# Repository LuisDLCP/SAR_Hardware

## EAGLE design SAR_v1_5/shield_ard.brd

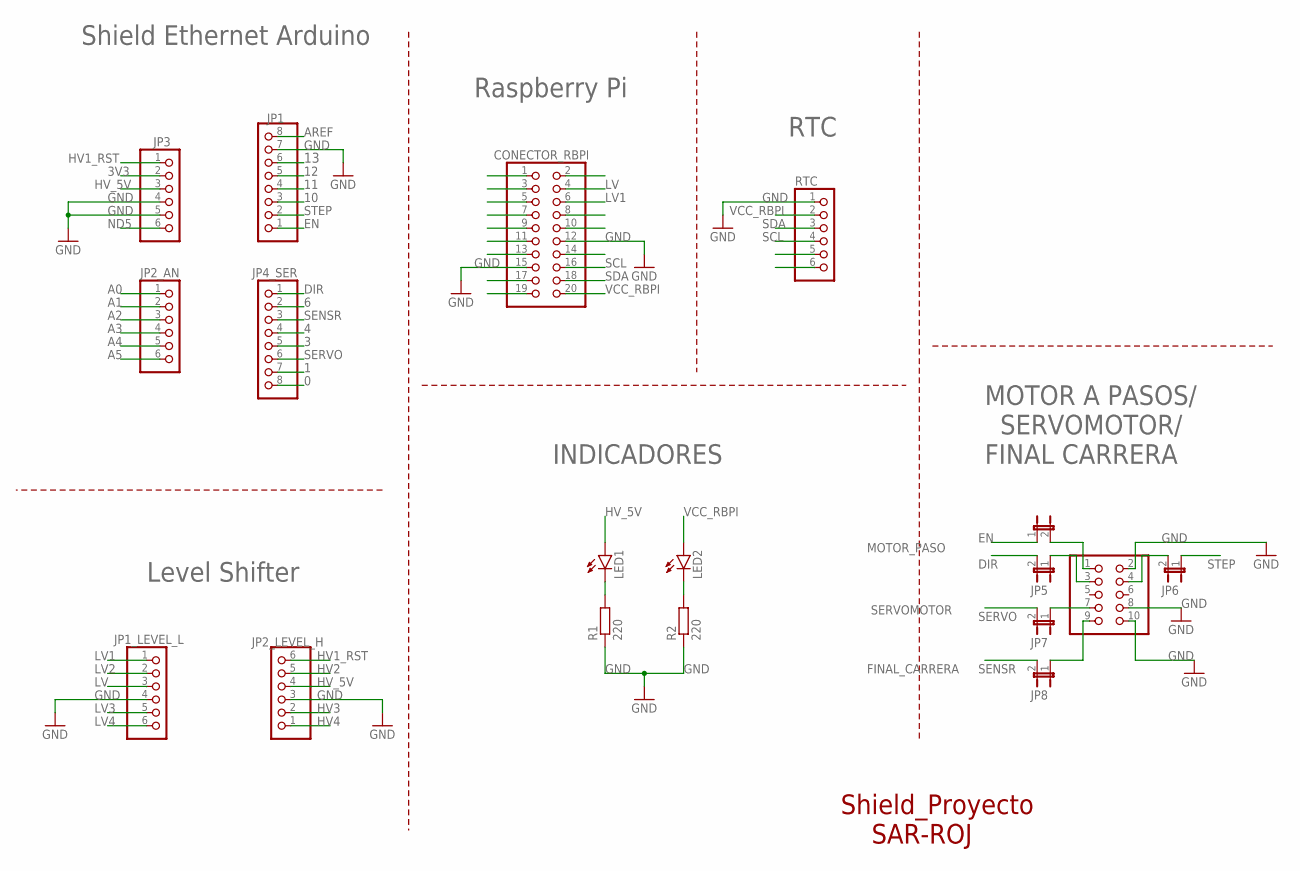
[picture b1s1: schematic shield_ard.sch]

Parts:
CONECTOR_RBPI: PINHD-2X10; 2X10
JP1, JP4_SER: PINHD-1X8; 1X08
JP1_LEVEL_L, JP2_AN, JP2_LEVEL_H, JP3: PINHD-1X6; 1X06
JP2, JP5, JP6, JP7, JP8: JUMPER-2PTH; 1X02
LED1, LED2: LEDCHIP-LED0805; CHIP-LED0805
MOTOR_PASO: PINHD-2X5; 2X05
R1, R2: 220; R0805
RTC: PINHD-1X6/90; 1X06/90

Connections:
0: JP4_SER.8
1: JP4_SER.7
3: JP4_SER.5
3V3: JP3.2
4: JP4_SER.4
6: JP4_SER.2
10: JP1.3
11: JP1.4
12: JP1.5
13: JP1.6
A0: JP2_AN.1
A1: JP2_AN.2
A2: JP2_AN.3
A3: JP2_AN.4
A4: JP2_AN.5
A5: JP2_AN.6
AREF: JP1.8
DIR: JP4_SER.1, JP5.1, JP5.2, MOTOR_PASO.3
EN: JP1.1, JP2.1, JP2.2, MOTOR_PASO.1
GND: CONECTOR_RBPI.12, CONECTOR_RBPI.15, JP1.7, JP1_LEVEL_L.4, JP2_LEVEL_H.3, JP3.4, JP3.5, MOTOR_PASO.2, MOTOR_PASO.8, MOTOR_PASO.10, R1.1, R2.1, RTC.1
HV1_RST: JP2_LEVEL_H.6, JP3.1
HV2: JP2_LEVEL_H.5
HV3: JP2_LEVEL_H.2
HV4: JP2_LEVEL_H.1
HV_5V: JP2_LEVEL_H.4, JP3.3, LED1.A
LV: CONECTOR_RBPI.4, JP1_LEVEL_L.3
LV1: CONECTOR_RBPI.6, JP1_LEVEL_L.1
LV2: JP1_LEVEL_L.2
LV3: JP1_LEVEL_L.5
LV4: JP1_LEVEL_L.6
unnamed: LED1.C, R1.2
unnamed: LED2.C, R2.2
unnamed: JP6.2, MOTOR_PASO.4
unnamed: JP7.1, MOTOR_PASO.7
ND5: JP3.6
SCL: CONECTOR_RBPI.16, RTC.4
SDA: CONECTOR_RBPI.18, RTC.3
SENSR: JP4_SER.3, JP8.1, JP8.2, MOTOR_PASO.9
SERVO: JP4_SER.6, JP7.2
STEP: JP1.2, JP6.1
VCC_RBPI: CONECTOR_RBPI.20, LED2.A, RTC.2

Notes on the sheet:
SERVOMOTOR
FINAL_CARRERA
Shield Ethernet Arduino
Level Shifter
Raspberry Pi
RTC
MOTOR A PASOS/ SERVOMOTOR/ FINAL CARRERA
INDICADORES
Shield_Proyecto SAR-ROJ

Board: 2 copper layers, 18 parts (1 on the bottom side), 17 nets, no tracks yet.

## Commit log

2019-11-16 the first files of PCBv1.5 were created
2019-11-16 a little change
2019-11-25 many componentes were placed in other position on the board
2019-11-25 cambios minimos
2019-11-30 all the componentes were placed and routed correctly
2019-11-30 brd file was added
2020-01-13 se cambio la posicion del Level Shifter
2020-01-25 a filter circuit was added to servomotor control circuit in order to avoid noise in control pin

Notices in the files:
parts and their libraries:
SparkFun-Retired: Licensing: Creative Commons ShareAlike 4.0 International - https://creativecommons.org/licenses/by-sa/4.0
